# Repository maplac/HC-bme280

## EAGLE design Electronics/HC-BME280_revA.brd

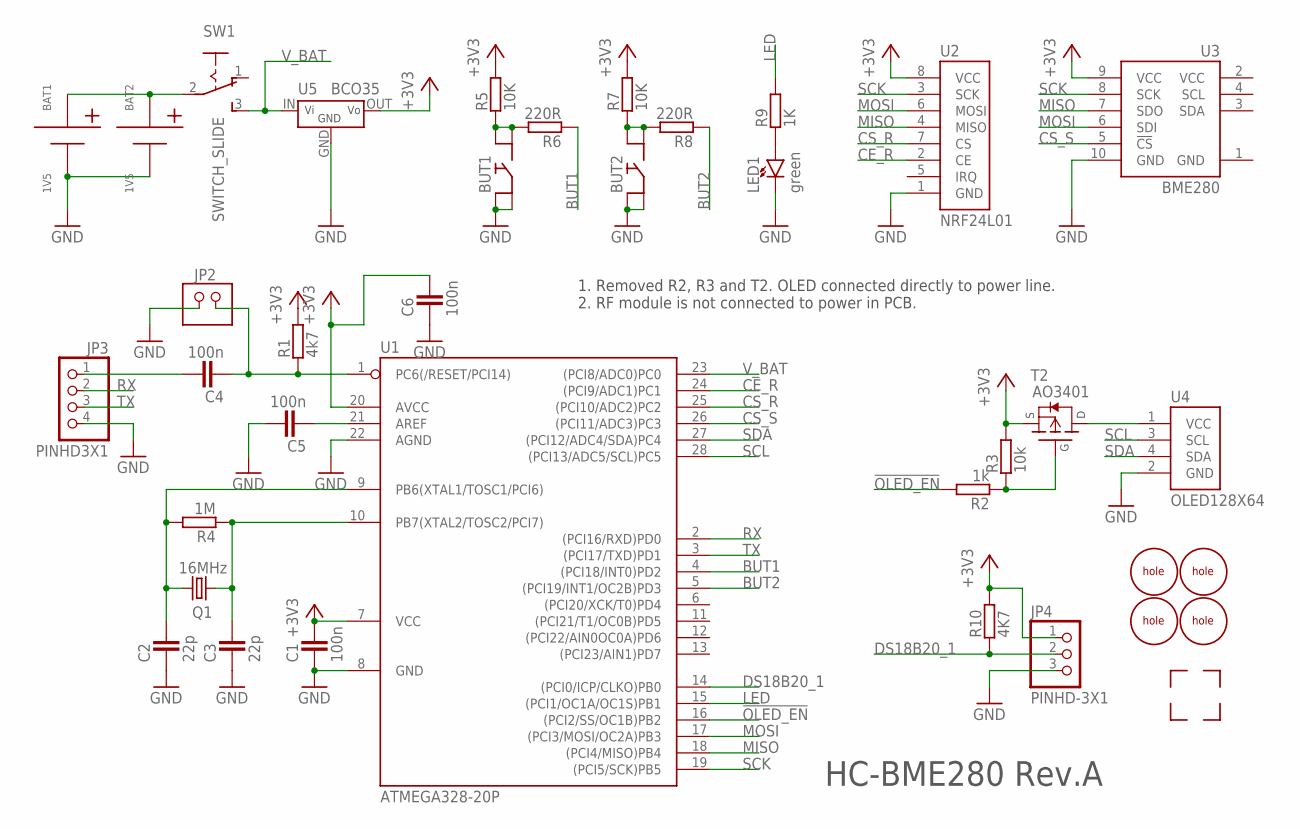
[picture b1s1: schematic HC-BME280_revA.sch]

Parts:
BAT1, BAT2: 1V5; 1XAA_BATTERY_HOLDER
BUT1, BUT2: BUTTON'THT'; BUTTON
C1, C4, C5, C6: 100n; C0805
C2, C3: 22p; C0805
JP2: PINHD2X1; PINHD-2X1
JP3: PINHD3X1; PINHD-4X1-90
JP4: PINHD-3X1
LED1: green; LED0805
Q1: 16MHz; HC49/S
R1: 4k7; R0805
R2: 1k; R0805
R3: 10k; R0805
R4: 1M; R0805
R5, R7: 10K; R0805
R6, R8: 220R; R0805
R9: 1K; R0805
R10: 4K7; R0805
SW1: SWITCH_SLIDE; SLIDE_SWITCH
T2: AO3401; SOT23
U1: ATMEGA328-20P; DIL28-3
U2: NRF24L01
U3: BME280
U4: OLED128X64
U5: BCO35
U$1, U$2, U$3, U$4: CORNER
U$5, U$6, U$7, U$8: HOLE

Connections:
!OLED_EN: R2.2, U1.16 ((PCI2/SS/OC1B)PB2)
+3V3: C1.2, C6.2, JP4.1, R1.2, R3.2, R5.2, R7.2, R10.2, T2.2 (S), U1.7 (VCC), U1.20 (AVCC), U2.8 (VCC), U3.9 (VCC), U5.OUT (VOUT)
BUT1: R6.1, U1.4 ((PCI18/INT0)PD2)
BUT2: R8.1, U1.5 ((PCI19/INT1/OC2B)PD3)
CE_R: U1.24 ((PCI9/ADC1)PC1), U2.2 (CE)
CS_R: U1.25 ((PCI10/ADC2)PC2), U2.7 (CS)
CS_S: U1.26 ((PCI11/ADC3)PC3), U3.5 (!CS)
DS18B20_1: JP4.2, R10.1, U1.14 ((PCI0/ICP/CLKO)PB0)
GND: BAT1.N, BAT2.N, BUT1.2, BUT1.4, BUT2.2, BUT2.4, C1.1, C2.1, C3.1, C5.2, C6.1, JP2.1, JP3.4, JP4.3, LED1.2 (K), U1.8 (GND), U1.22 (AGND), U2.1 (GND), U3.1 (GND), U3.10 (GND), U4.2 (GND), U5.GND
LED: R9.2, U1.15 ((PCI1/OC1A/OC1S)PB1)
MISO: U1.18 ((PCI4/MISO)PB4), U2.4 (MISO), U3.7 (SDO)
MOSI: U1.17 ((PCI3/MOSI/OC2A)PB3), U2.6 (MOSI), U3.6 (SDI)
unnamed: C3.2, Q1.1, R4.1, U1.10 (PB7(XTAL2/TOSC2/PCI7))
unnamed: C4.1, JP2.2, R1.1, U1.1 (PC6(/RESET/PCI14))
unnamed: R2.1, R3.1, T2.1 (G)
unnamed: C2.2, Q1.2, R4.2, U1.9 (PB6(XTAL1/TOSC1/PCI6))
unnamed: C5.1, U1.21 (AREF)
unnamed: C4.2, JP3.1
unnamed: T2.3 (D), U4.1 (VCC)
unnamed: BAT1.P, BAT2.P, SW1.2 (MIDDLE)
unnamed: BUT1.1, BUT1.3, R5.1, R6.2
unnamed: BUT2.1, BUT2.3, R7.1, R8.2
unnamed: LED1.1 (A), R9.1
RX: JP3.2, U1.2 ((PCI16/RXD)PD0)
SCK: U1.19 ((PCI5/SCK)PB5), U2.3 (SCK), U3.8 (SCK)
SCL: U1.28 ((PCI13/ADC5/SCL)PC5), U4.3 (SCL)
SDA: U1.27 ((PCI12/ADC4/SDA)PC4), U4.4 (SDA)
TX: JP3.3, U1.3 ((PCI17/TXD)PD1)
VCC: U3.2 (VCC)
V_BAT: SW1.3 (S), U1.23 ((PCI8/ADC0)PC0), U5.IN (VIN)

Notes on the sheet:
1. Removed R2, R3 and T2. OLED connected directly to power line. 2. RF module is not connected to power in PCB.
HC-BME280 Rev.A

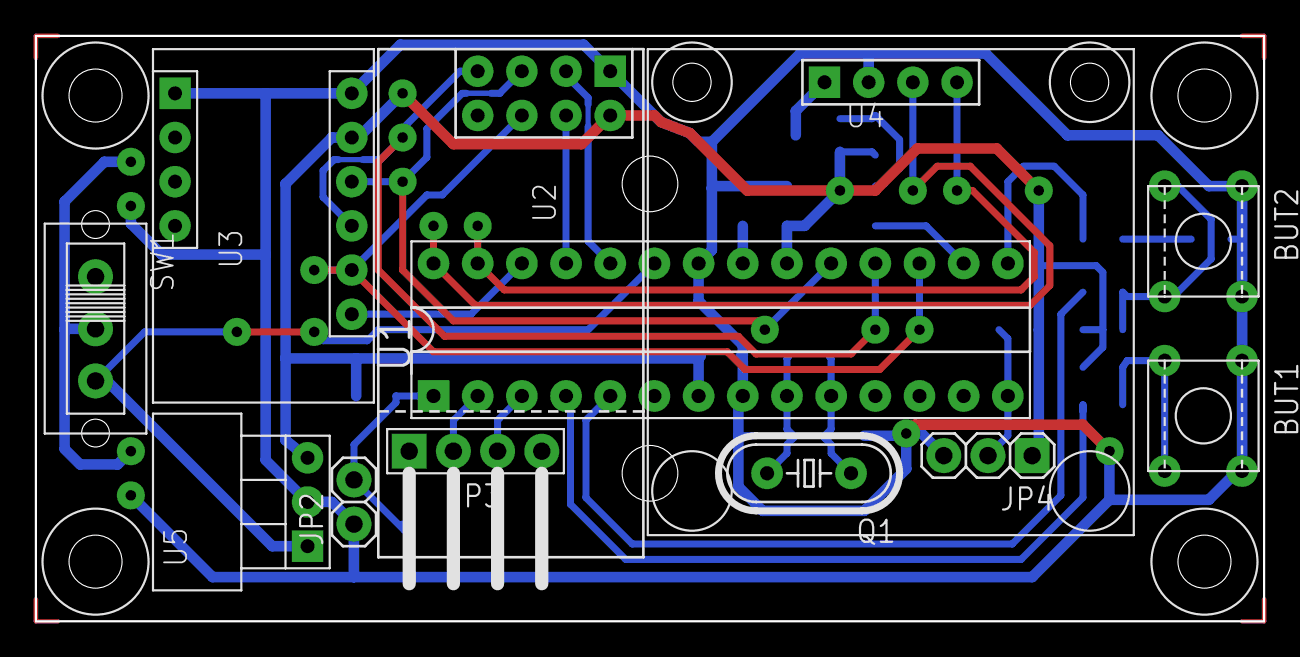
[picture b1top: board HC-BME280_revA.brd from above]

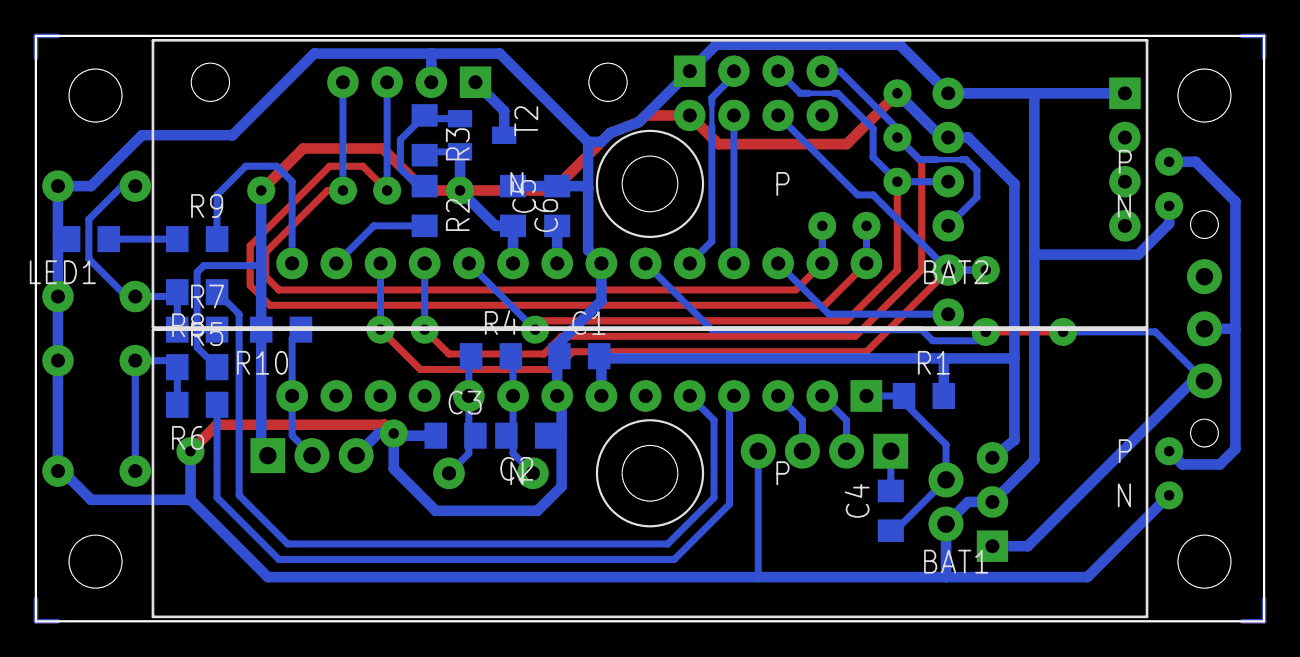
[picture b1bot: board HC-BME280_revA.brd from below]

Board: 2 copper layers, 70.6 x 33.7 mm, 40 parts (20 on the bottom side), 29 nets.

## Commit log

2017-05-23 added: arduino code for testing bme280 and nrf24l01
2017-06-03 changed: location of arduino libraries
2017-06-03 added: code for controlling OLED with SSD1306
2017-06-11 added: code for controlling DS18B20
2017-06-11 changed: BME280 switched to SPI interface
2017-06-11 changed: firmware code moved to appropriate folder
2017-06-11 added: circuit diagram
2017-07-14 modified: diagram and PCB
2017-07-15 modified: PCB
2017-07-16 modified: PCB - revA
2017-07-16 added: code for power saving features
2017-07-22 modified: minor changes in schematics and PCB
2017-08-05 changed: lots of changes in FW
2017-08-12 added: comments to schematic
2017-08-12 added: exported files for manufacturing the PCB
2017-08-13 modified: code cleanup
2017-08-13 fixed: packet counter
2017-08-15 fixed: the first packet is correctly transferred
2018-01-28 changed: measure period, values are send on button press
